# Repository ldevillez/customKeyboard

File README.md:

# customKeyboard

Improve tipping skills

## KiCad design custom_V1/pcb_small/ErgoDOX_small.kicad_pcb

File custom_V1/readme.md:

# V1
The V1 is based on the ergodox but with sone nice features
* USB C
* USB hub (2.0)
* Each half are independent
##

## subversions
* The "logic" version of the pcb is just the upper-part of it with all the logic(teensy, hub,leds) to have a smaller pcb. It would have been great to have it reduce under 10 mm. The all version is also there for the switch.

## Shopping list
<table>
  <thead>
    <tr>
    <th>Amount</th>
    <th>Part type</th>
    <th>Description</th>
    <th>Price (to pay)</th>
    <th>Link</th>
    </tr>
  </thead>
  <tbody>
    <tr>
      <th>2</th>
      <th>Teensy LC</th>
      <th> </th>
      <th>28.44</th>
      <th>https://www.digikey.be/product-detail/fr/sparkfun-electronics/DEV-13305/1568-1233-ND/5721428</th>
    </tr>
    <tr>
      <th>4</th>
      <th>Header 14*1 2.54mm</th>
      <th>For teensy</th>
      <th>2.4</th>
      <th>https://www.digikey.be/product-detail/en/w%C3%BCrth-elektronik/61301411121/732-5325-ND/4846849</th>
    </tr>
    <tr>
      <th>10</th>
      <th>Led jaune SMD</th>
      <th>For usb hub</th>
      <th>2.33</th>
      <th>https://www.digikey.be/product-detail/fr/qt-brightek-qtb/QBLP615-Y/1516-1077-1-ND/4814804</th>
    </tr>
    <tr>
      <th>16</th>
      <th>R smd 150</th>
      <th>R smd led</th>
      <th>3.6</th>
      <th>https://www.digikey.be/product-detail/fr/rohm-semiconductor/LTR18EZPF1500/RHM150YCT-ND/4055449</th>
    </tr>
    <tr>
      <th>8</th>
      <th>R smd 4.99k</th>
      <th>For usb type C </th>
      <th>2.36</th>
      <th>https://www.digikey.be/product-detail/fr/vishay-dale/RCL06124K99FKEA/541-2378-1-ND/2587746</th>
    </tr>
    <tr>
      <th>2</th>
      <th>R smd 2.7k</th>
      <th>Usb hub</th>
      <th>0.26</th>
      <th>https://www.digikey.be/product-detail/fr/rohm-semiconductor/LTR18EZPF2701/RHM2-70KYCT-ND/1973120</th>
    </tr>
    <tr>
      <th>2</th>
      <th>Connector USB A</th>
      <th></th>
      <th>0.78</th>
      <th>https://www.digikey.be/product-detail/fr/on-shore-technology-inc/USB-A1HSW6/ED2989-ND/2677750</th>
    </tr>
    <tr>
      <th>4</th>
      <th>Connector USB C</th>
      <th></th>
      <th>2.52</th>
      <th>https://www.digikey.be/product-detail/fr/cvilux-usa/CU3216SASBLR004-NH/2987-CU3216SASBLR004-NHCT-ND/13177603</th>
    </tr>
    <tr>
      <th>6</th>
      <th>USBLC6</th>
      <th>Protect device when connecting usb</th>
      <th>2.01</th>
      <th>https://www.digikey.be/product-detail/fr/stmicroelectronics/USBLC6-2SC6/497-5235-1-ND/1121688</th>
    </tr>
    <tr>
      <th>10</th>
      <th>Led TH</th>
      <th>Only use 1 pin</th>
      <th>2.26</th>
      <th>https://www.digikey.be/product-detail/fr/lite-on-inc/LTL-1BEHJ/160-1938-ND/3198396</th>
    </tr>
    <tr>
      <th>4</th>
      <th>C 10u</th>
      <th></th>
      <th>0.92</th>
      <th>https://www.digikey.be/product-detail/fr/avx-corporation/12061C103KAZ2A/478-3577-1-ND/1024930</th>
    </tr>
    <tr>
      <th>2</th>
      <th>R 510</th>
      <th></th>
      <th>0.22</th>
      <th>https://www.digikey.be/product-detail/fr/rohm-semiconductor/LTR18EZPJ511/RHM510ZCT-ND/1973140</th>
    </tr>
    <tr>
      <th>2</th>
      <th>74LS14 N</th>
      <th>Porte logique</th>
      <th>0.98</th>
      <th>https://www.digikey.be/product-detail/fr/texas-instruments/SN74LS14DBR/296-26505-1-ND/2255024</th>
    </tr>
    <tr>
      <th>100</th>
      <th>Diodes SMD</th>
      <th></th>
      <th>3.99</th>
      <th>https://www.digikey.be/product-detail/fr/on-semiconductor/MMSD4148T1G/MMSD4148T1GOSCT-ND/1121611</th>
    </tr>
    <tr>
      <th>100</th>
      <th>Diodes </th>
      <th>Alt to smd ones</th>
      <th>2.06</th>
      <th>https://www.digikey.be/product-detail/fr/on-semiconductor/1N4148/1N4148FS-ND/458603</th>
    </tr>
    <tr>
      <th>88</th>
      <th>Cherry MX brown</th>
      <th></th>
      <th>30.92</th>
      <th>https://fr.aliexpress.com/item/1005001681627152.html?spm=a2g0o.productlist.0.0.4b9e49a1pXCVAw&algo_pvid=aae6ed30-4209-492e-a736-7e098fa6cffb&algo_expid=aae6ed30-4209-492e-a736-7e098fa6cffb-18&btsid=0bb0622a16102183873605978e7444&ws_ab_test=searchweb0_0,searchweb201602_,searchweb201603_</th>
    </tr>
    <tr>
      <th>1</th>
      <th>Cable ubs C-C 3.0</th>
      <th>Need 3.0 not 2.0 </th>
      <th>9.10</th>
      <th>https://www.digikey.be/product-detail/fr/cui-devices/CBLT-UC-UC-1WT/102-5955-ND/9838607</th>
    </tr>
    <tr>
      <th>2</th>
      <th>IC Hub usb 2.0 </th>
      <th></th>
      <th>3</th>
      <th>https://fr.aliexpress.com/item/33046559993.html?spm=a2g0o.cart.0.0.79213c00v1W7BP&mp=1</th>
    </tr>
    <tr>
    <th>Total</th>
    <th></th>
    <th></th>
    <th> 90.69 </th>
    <th></th>
  </tbody>
</table>

### Switch
I don't really know which switch fit me the best so i prefer buy cheap one for the prototype and remplace them later with **real** cherry mx. For example https://www.digikey.com/en/products/detail/cherry-americas-llc/MX1A-E1NW/20180?s=N4IgjCBcoLQBxVAYygMwIYBsDOBTANCAPZQDa4AbACxUgC6Avg4QExkgCyAGmAIIwBRMADkA6vQZA

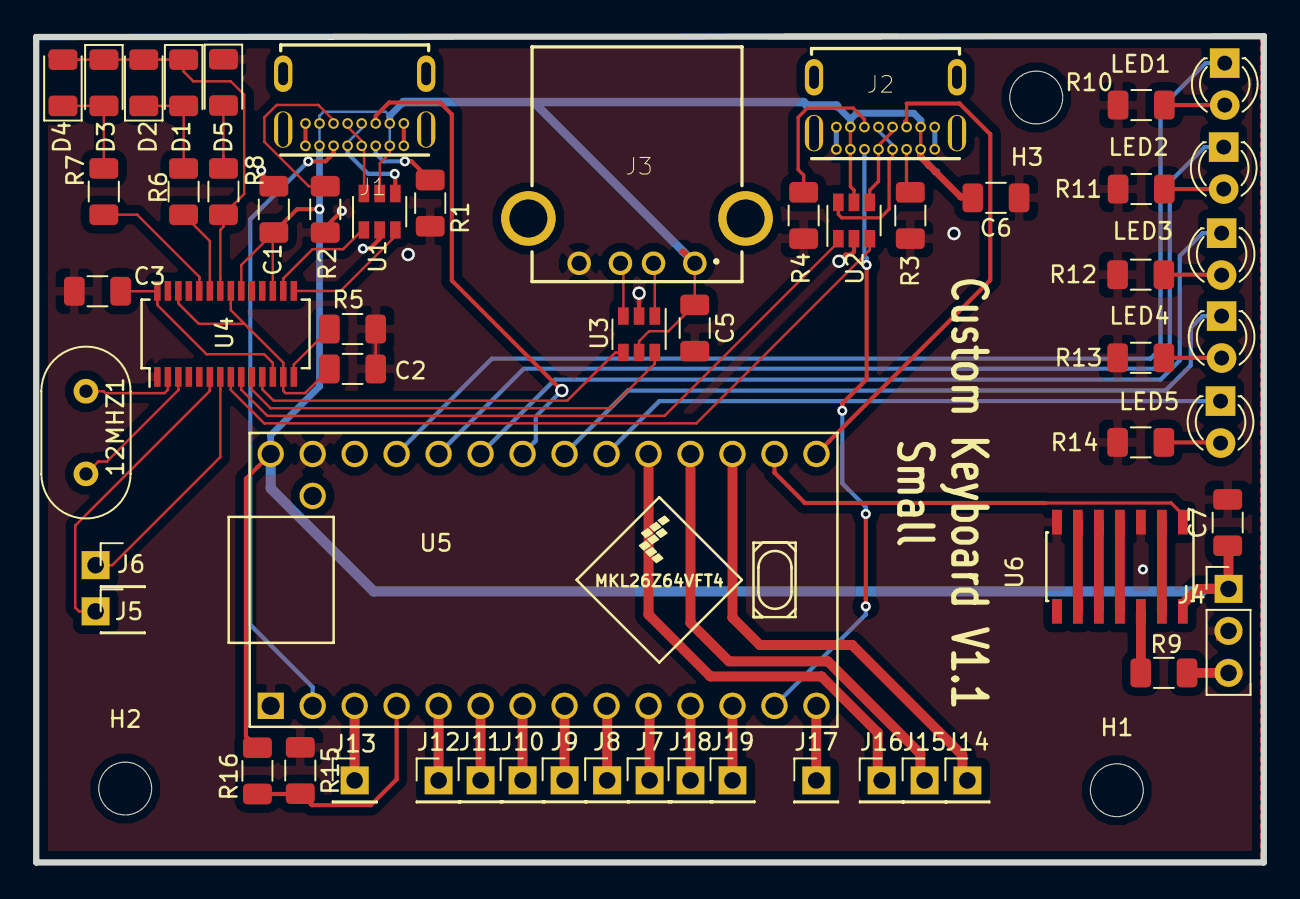
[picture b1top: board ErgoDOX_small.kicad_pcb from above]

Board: 2 copper layers, 74.3 x 50.0 mm, 61 parts (0 on the bottom side), 66 nets.

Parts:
12MHZ1: Crystal; Resonator-2Pin_W10.0mm_H5.0mm
C1, C2, C3: 10u; C_1206_3216Metric
C5, C6, C7: 1u; C_1206_3216Metric
D1, D2, D3, D4, D5: D; LED_1206_3216Metric
H1: MountingHole; MountingHole_3.2mm_M3_DIN965
H2, H3: MountingHole; MountingHole_3.2mm_M3
J1: Input; GCT_USB4085-GF-A_REVA
J2: OutputC; GCT_USB4085-GF-A_REVA
J3: OutputA; 61400416021
J4: Conn_01x03; PinHeader_1x03_P2.54mm_Vertical
J5, J6, J7, J8, J9, J10, J11, J12, J13, J14, J15, J16, J17, J18, J19: Conn_01x01; PinHeader_1x01_P2.54mm_Vertical
LED1: LED1; LED_D3.0mm
LED2: LED2; LED_D3.0mm
LED3: LED3; LED_D3.0mm
LED4: LED4; LED_D3.0mm
LED5: LED5; LED_D3.0mm
R1, R2, R3, R4: 5.1k; R_1206_3216Metric
R5: 2.7k; R_1206_3216Metric
R6, R7, R8, R10, R11, R12, R13, R14: 150; R_1206_3216Metric
R9: 510; R_1206_3216Metric
R15, R16: 10k; R_1206_3216Metric
U1, U2, U3: USBLC6-2SC6; SOT-23-6
U4: FE1.1s; SSOP-28_3.9x9.9mm_P0.635mm
U5: Teensy-LC; Teensy_LC_CUSTOM_EDIT
U6: 74LS14; SOIC-14_3.9x8.7mm_P1.27mm

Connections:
+5V: C1.1, C5.2, C6.2, C7.1, J1.A4, J1.A9, J1.B4, J1.B9, J2.A4, J2.A9, J2.B4, J2.B9, J3.1, J4.1, R16.1, U1.5, U2.5, U3.5, U4.17, U4.20, U5.33, U6.14
/COL0: J7.1, U5.10
/COL1: J8.1, U5.9
/COL2: J9.1, U5.8
/COL3: J10.1, U5.7
/COL4: J11.1, U5.6
/COL5: J12.1, U5.5
/COL6: J13.1, U5.3
/ROW0: J14.1, U5.22
/ROW1: J15.1, U5.23
/ROW2: J16.1, U5.24
/ROW3: J17.1, U5.14
/ROW4: J19.1, U5.12
/ROW5: J18.1, U5.11
GND: C1.2, C2.2, C3.2, C5.1, C6.1, C7.2, D5.1, J1.A1, J1.A12, J1.B1, J1.B12, J2.A1, J2.A12, J2.B1, J2.B12, J3.4, J4.2, R1.2, R2.2, R3.2, R4.2, R5.2, R10.2, R11.2, R12.2, R13.2, R14.2, R15.1, U1.2, U2.2, U3.2, U4.1, U5.1, U5.32, U6.3, U6.7
INPUT_USB_CONN_D+: J1.A6, J1.B6, U1.6
INPUT_USB_CONN_D-: J1.A7, J1.B7, U1.4
INPUT_USB_D+: U1.1, U4.16
INPUT_USB_D-: U1.3, U4.15
L1: LED1.1, U5.30
L2: LED2.1, U5.29
L3: LED3.1, U5.28
L4: LED4.1, U5.26
L5: LED5.1, U5.25
LED_BACKLIGHT_33V: U5.21, U6.1
MOSI_IN: J1.A8, U5.2
MOSI_OUT: J2.A8, U5.13
unnamed: 12MHZ1.1, U4.3
unnamed: 12MHZ1.2, U4.2
unnamed: D1.1, D2.2, D3.1, D4.2, R8.2, U4.22
unnamed: D1.2, D2.1, R6.1
unnamed: D3.2, D4.1, R7.1
unnamed: D5.2, R8.1
unnamed: J1.A5, R1.1
unnamed: J1.B5, R2.1
unnamed: J1.P1, J1.P2, J1.P3, J1.P4
unnamed: J2.A5, R3.1
unnamed: J2.B5, R4.1
unnamed: J2.P1, J2.P2, J2.P3, J2.P4
unnamed: J4.3, R9.1
unnamed: LED1.2, R10.1
unnamed: LED2.2, R11.1
unnamed: LED3.2, R12.1
unnamed: LED4.2, R13.1
unnamed: LED5.2, R14.1
unnamed: R5.1, U4.14
unnamed: R6.2, U4.23
unnamed: R7.2, U4.24
unnamed: R9.2, U6.12
unnamed: R15.2, R16.2, U5.4
unnamed: U6.6, U6.9
unnamed: U6.5, U6.10
unnamed: U6.4, U6.11
unnamed: U6.2, U6.13
OUTPUTA_USB_CONN_D+: J3.3, U3.3
OUTPUTA_USB_D+: U3.4, U4.11
OUTPUTC_USB_CONN_D+: J2.A6, J2.B6, U2.6
OUTPUTC_USB_CONN_D-: J2.A7, J2.B7, U2.4
OUTPUTC_USB_D+: U2.1, U4.9
OUTPUTC_USB_D-: U2.3, U4.8
SCK_IN: J1.B8, U5.27
SCK_OUT: J2.B8, U5.20
TEENSY_USB_D+: J6.1, U4.7
TEENSY_USB_D-: J5.1, U4.6
VD18: C3.1, U4.12, U4.28
VD33: C2.1, U4.13, U4.21, U4.26

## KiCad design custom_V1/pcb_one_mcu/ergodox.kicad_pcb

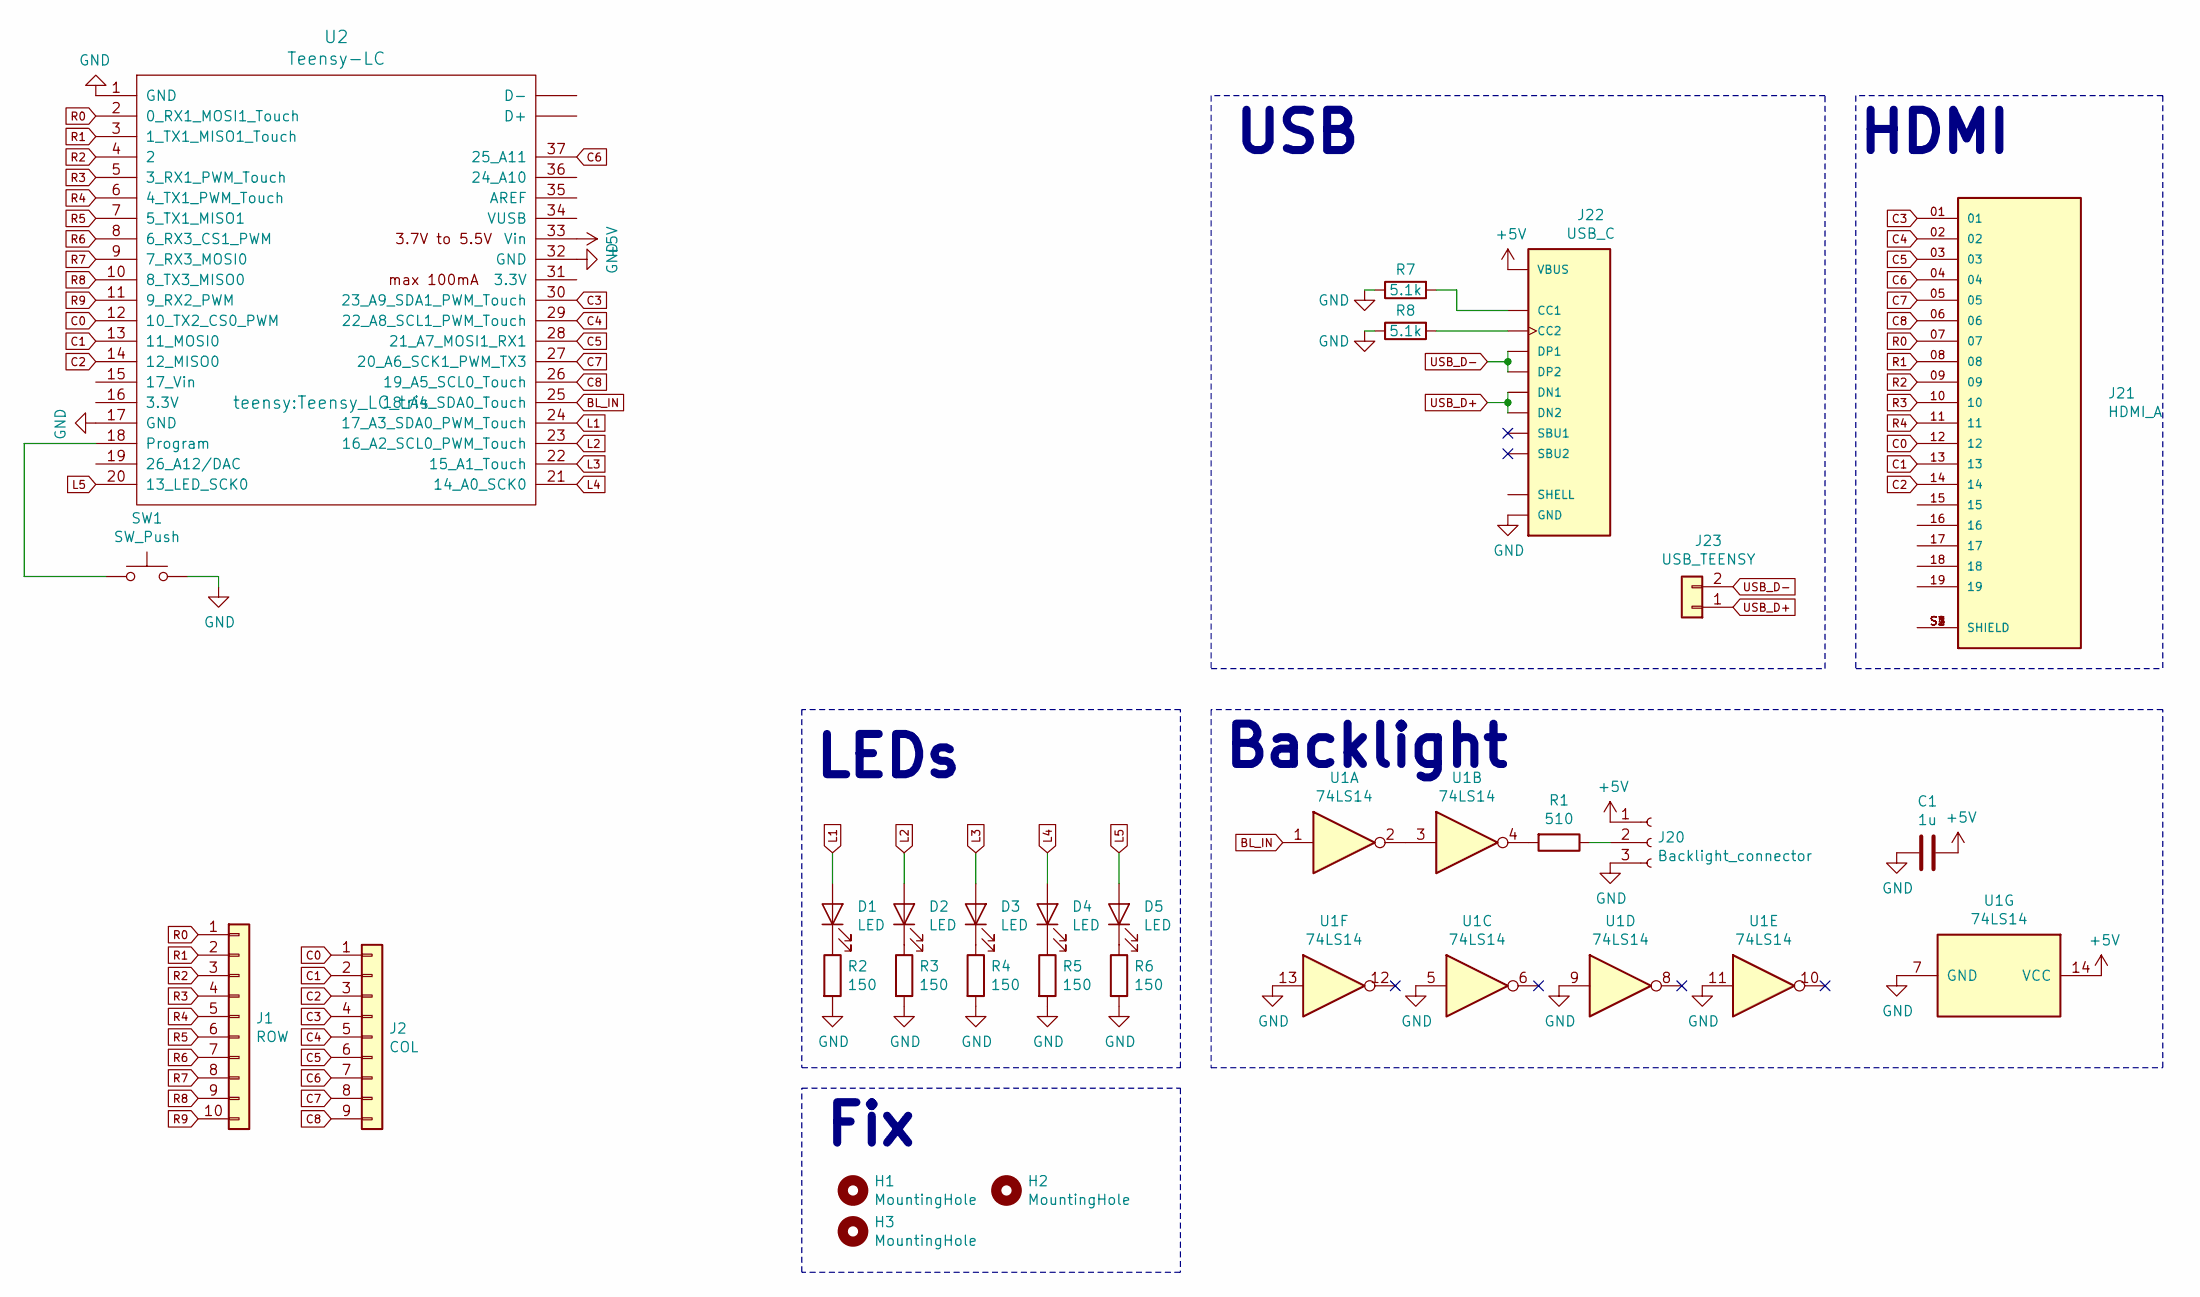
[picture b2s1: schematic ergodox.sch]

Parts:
C1: 1u; C_1206_3216Metric
D1, D2, D3, D4, D5: LED; LED_D3.0mm
H1, H2, H3: MountingHole; MountingHole_2.5mm
J1: ROW; PinHeader_1x10_P2.54mm_Vertical
J2: COL; PinHeader_1x09_P2.54mm_Vertical
J20: Backlight_connector; PinHeader_1x03_P2.54mm_Vertical
J21: HDMI_A; SAMTEC_HDMR-19-02-S-SM
J22: USB_C; GCT_USB4085-GF-A_REVA
J23: USB_TEENSY; PinHeader_1x02_P2.54mm_Vertical
R1: 510; R_1206_3216Metric
R2, R3, R4, R5, R6: 150; R_1206_3216Metric
R7, R8: 5.1k; R_1206_3216Metric
SW1: SW_Push; SW_Tactile_SPST_Angled_PTS645Vx39-2LFS
U1: 74LS14; SOIC-14_3.9x8.7mm_P1.27mm
U2: Teensy-LC; Teensy_LC_tris

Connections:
+5V: C1.1, J20.1, J22.A4 (VBUS), J22.A9 (VBUS), J22.B4 (VBUS), J22.B9 (VBUS), U1.14 (VCC), U2.33 (Vin)
BL_IN: U1.1, U2.25 (18_A4_SDA0_Touch)
C0: J2.1, J21.12, U2.12 (10_TX2_CS0_PWM)
C1: J2.2, J21.13, U2.13 (11_MOSI0)
C2: J2.3, J21.14, U2.14 (12_MISO0)
C3: J2.4, J21.01, U2.30 (23_A9_SDA1_PWM_Touch)
C4: J2.5, J21.02, U2.29 (22_A8_SCL1_PWM_Touch)
C5: J2.6, J21.03, U2.28 (21_A7_MOSI1_RX1)
C6: J2.7, J21.04, U2.37 (25_A11)
C7: J2.8, J21.05, U2.27 (20_A6_SCK1_PWM_TX3)
C8: J2.9, J21.06, U2.26 (19_A5_SCL0_Touch)
GND: C1.2, J20.3, J22.A1 (GND), J22.A12 (GND), J22.B1 (GND), J22.B12 (GND), R2.2, R3.2, R4.2, R5.2, R6.2, R7.1, R8.1, SW1.2, U1.5, U1.7 (GND), U1.9, U1.11, U1.13, U2.1 (GND), U2.17 (GND), U2.32 (GND)
L1: D1.2 (A), U2.24 (17_A3_SDA0_PWM_Touch)
L2: D2.2 (A), U2.23 (16_A2_SCL0_PWM_Touch)
L3: D3.2 (A), U2.22 (15_A1_Touch)
L4: D4.2 (A), U2.21 (14_A0_SCK0)
L5: D5.2 (A), U2.20 (13_LED_SCK0)
unnamed: D1.1 (K), R2.1
unnamed: D2.1 (K), R3.1
unnamed: D3.1 (K), R4.1
unnamed: D4.1 (K), R5.1
unnamed: D5.1 (K), R6.1
unnamed: J20.2, R1.1
unnamed: J21.S1 (SHIELD), J21.S2 (SHIELD), J21.S3 (SHIELD), J21.S4 (SHIELD)
unnamed: J22.A5 (CC1), R7.2
unnamed: J22.B5 (CC2), R8.2
unnamed: J22.P1 (SHELL), J22.P2 (SHELL), J22.P3 (SHELL), J22.P4 (SHELL)
unnamed: R1.2, U1.4
unnamed: SW1.1, U2.18 (Program)
unnamed: U1.2, U1.3
R0: J1.1, J21.07, U2.2 (0_RX1_MOSI1_Touch)
R1: J1.2, J21.08, U2.3 (1_TX1_MISO1_Touch)
R2: J1.3, J21.09, U2.4 (2)
R3: J1.4, J21.10, U2.5 (3_RX1_PWM_Touch)
R4: J1.5, J21.11, U2.6 (4_TX1_PWM_Touch)
R5: J1.6, U2.7 (5_TX1_MISO1)
R6: J1.7, U2.8 (6_RX3_CS1_PWM)
R7: J1.8, U2.9 (7_RX3_MOSI0)
R8: J1.9, U2.10 (8_TX3_MISO0)
R9: J1.10, U2.11 (9_RX2_PWM)
USB_D+: J22.A7 (DN1), J22.B7 (DN2), J23.1
USB_D-: J22.A6 (DP1), J22.B6 (DP2), J23.2

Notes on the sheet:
Backlight
LEDs
Fix
HDMI
USB

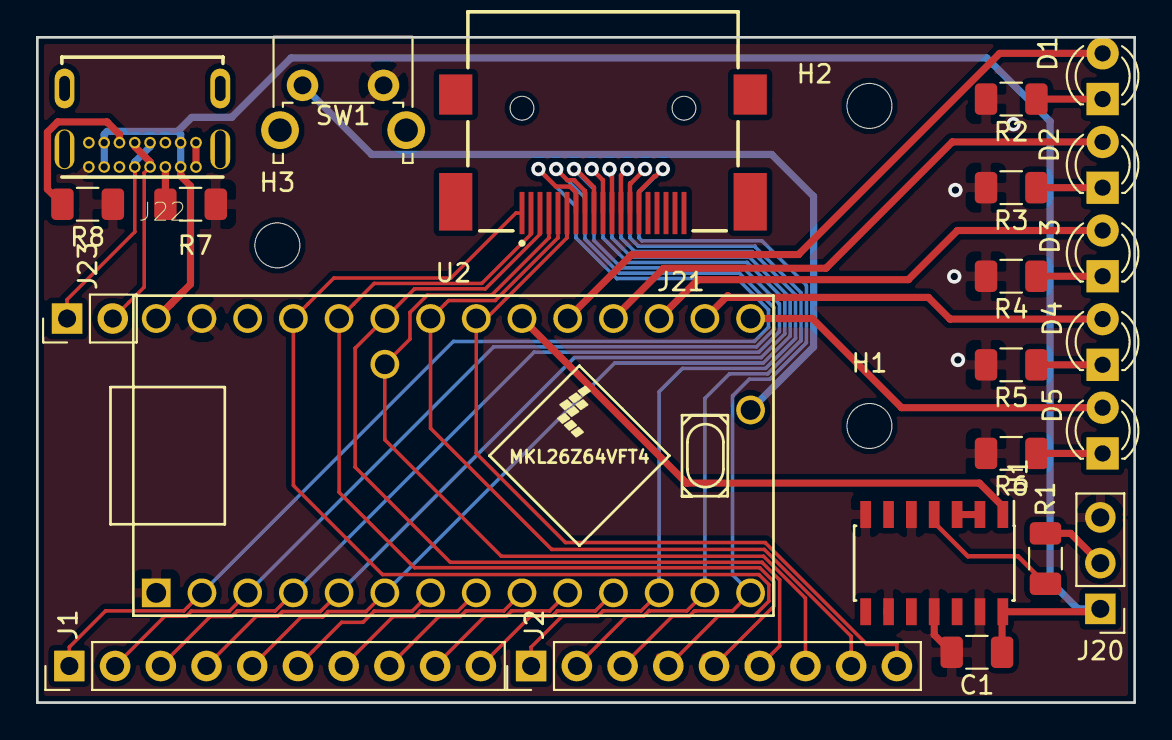
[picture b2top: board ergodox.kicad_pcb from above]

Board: 2 copper layers, 61.0 x 37.0 mm, 26 parts (0 on the bottom side), 42 nets.

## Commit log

2021-01-13 first version
2021-01-13 add logic version for V1
2021-01-13 typo readme
2021-01-13 missing headers
2021-01-19 add step of custom
2021-02-27 add V1.1 pcb
2021-03-21 big updates
2021-05-21 fix flawn in design
2021-07-03 push
2021-11-21 add 1 mcu
